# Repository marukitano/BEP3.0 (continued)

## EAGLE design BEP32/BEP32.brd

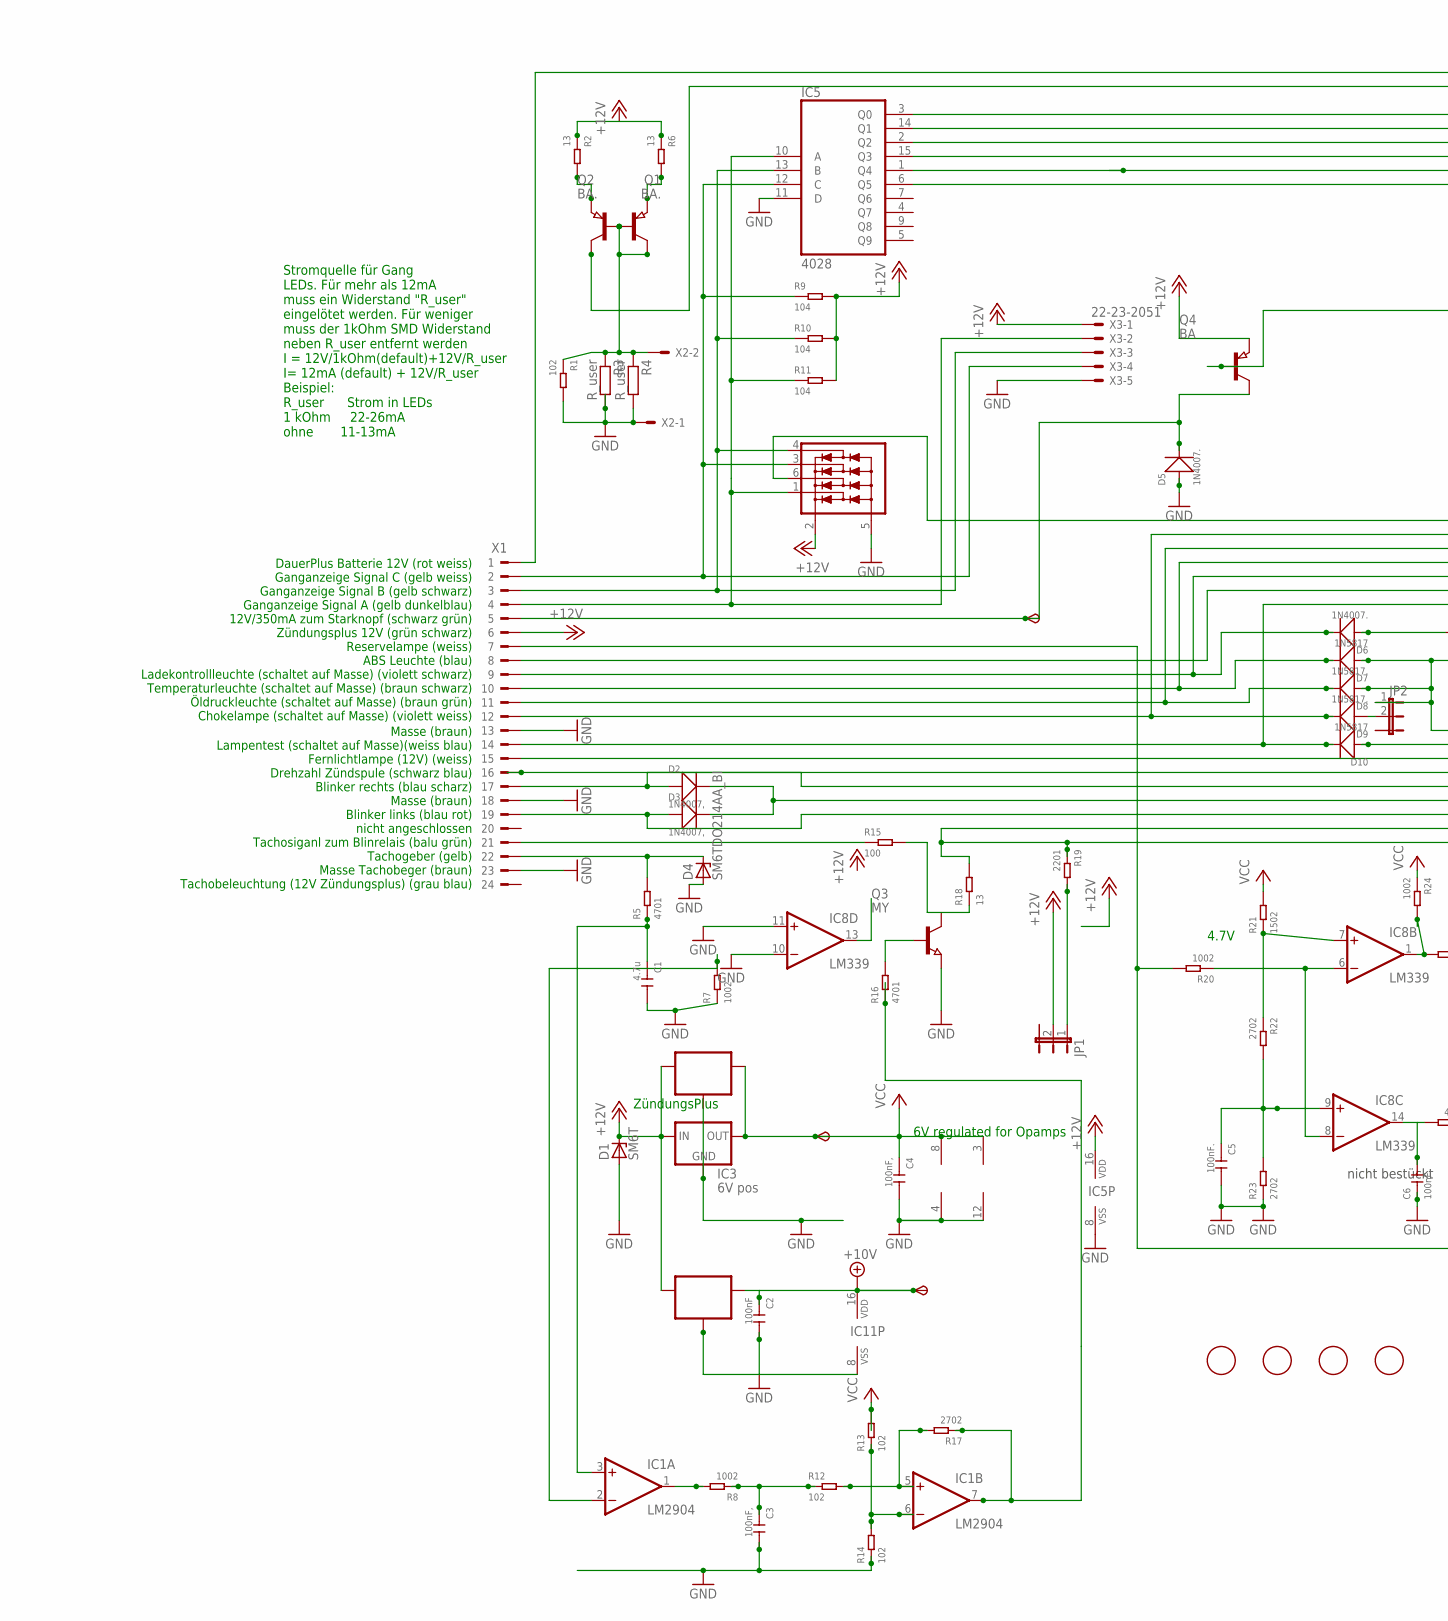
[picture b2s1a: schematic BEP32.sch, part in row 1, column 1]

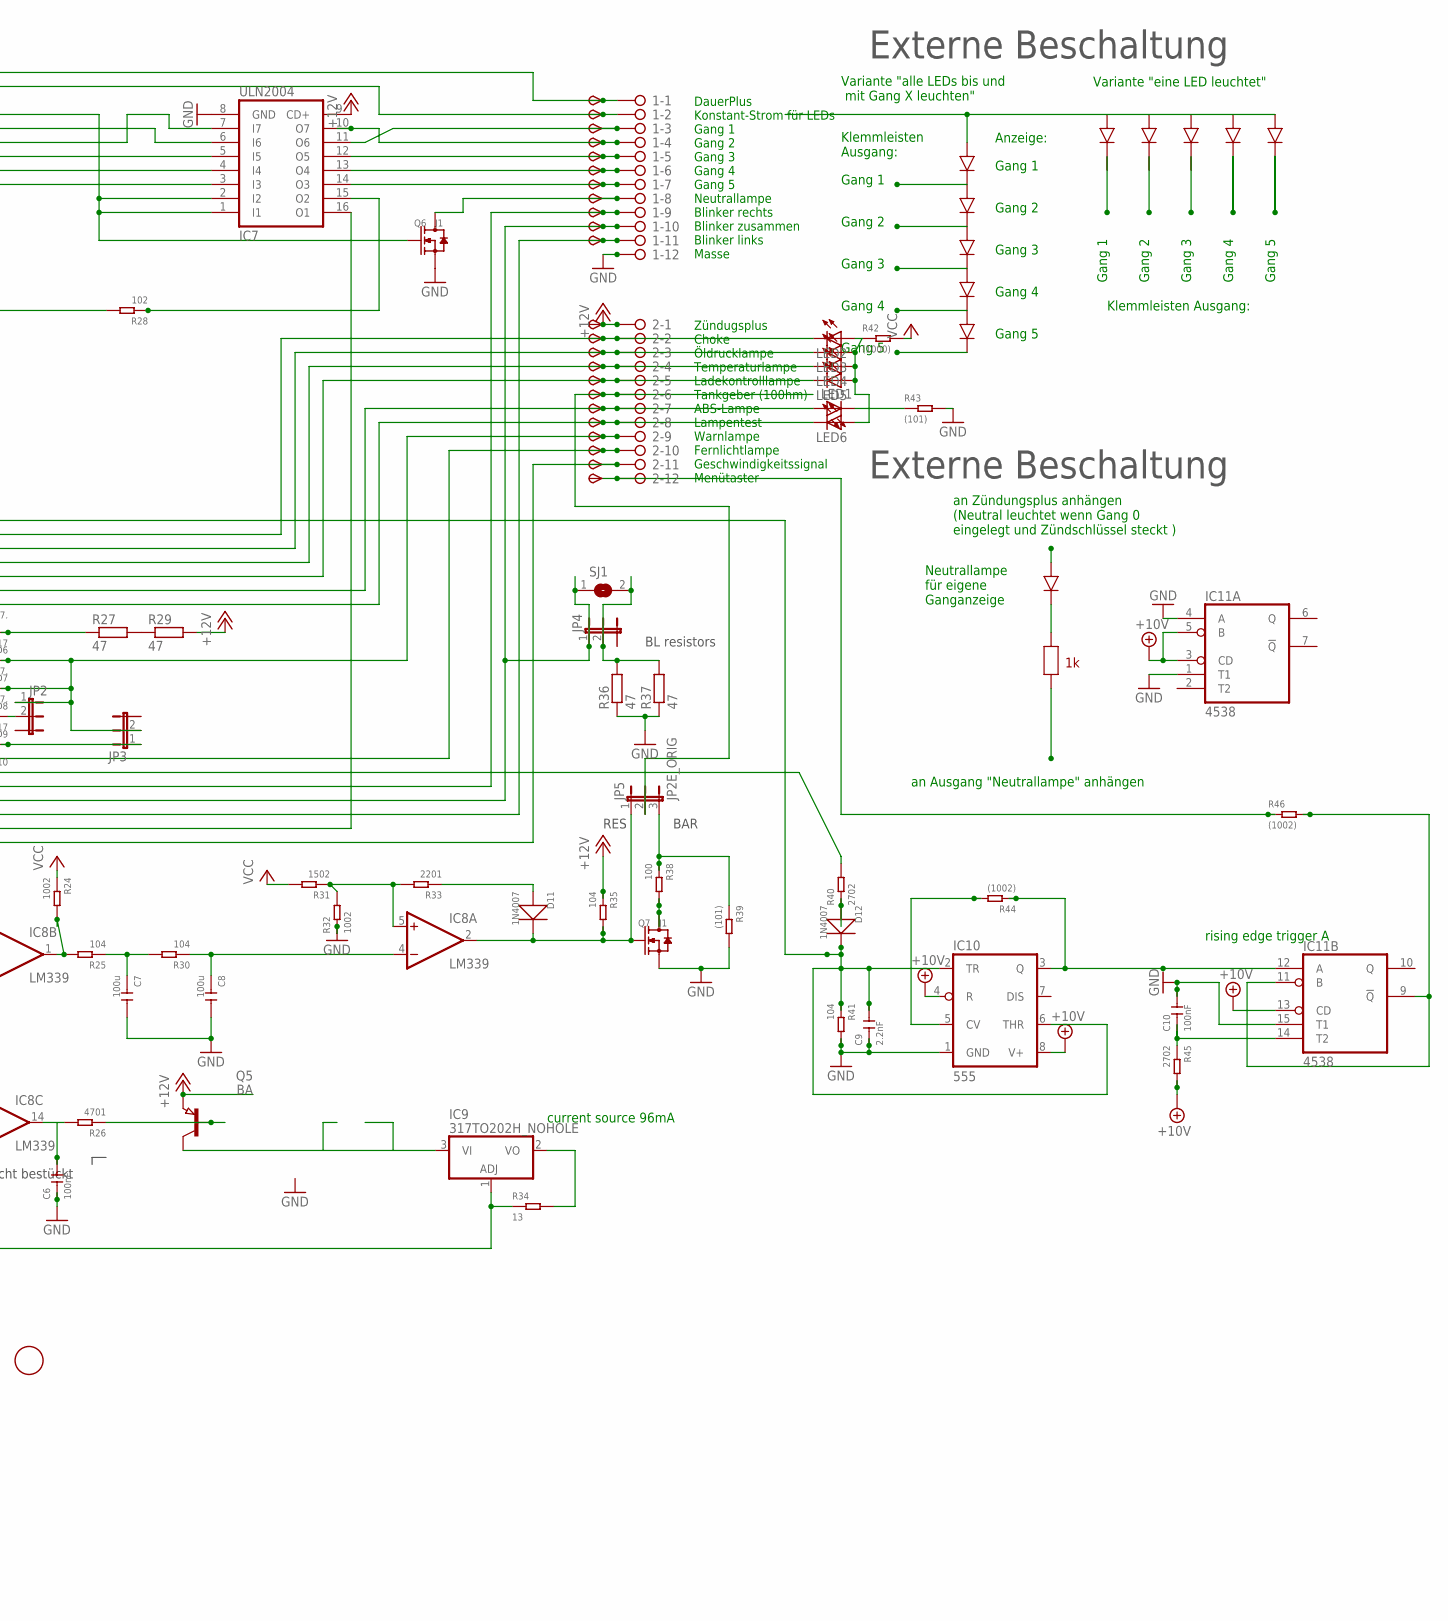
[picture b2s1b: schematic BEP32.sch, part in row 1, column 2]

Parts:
1, 2: 2081-1132; 12-PIN
6V, 10V: TPSB2.0; B2.0
C1: 4.7u; C0805
C2, C10: 100nF; C0805
C3, C4: 100nF,; C0805
C5, C6: 100nF.; C0805
C7, C8: 100u; C1206
C9: 2.2nF; C0805
D1: SM6T; DO214AA
D2, D3: 1N4007,; DO-214AC
D4: SM6TDO214AA_BI; DO214AA_BI
D5, D6: 1N4007.; DO-214AC
D7, D10: 1N5817; DO-214AC_SLIM
D8, D9: 1N5817.; DO-214AC_SLIM
D11, D12: 1N4007; DO-214AC
FID1, FID2, FID3, FID4: FIDUCIAL; FIDUCIAL_1MM
IC1: LM2904; SO08
IC2: 78L06; SOT89_ROUND
IC3: 6V pos; 78LXX
IC4: 78L10; SOT89_ROUND
IC5: 4028; SO16
IC6: NUP4304SOT457_R; SOT457R_PHILIPS
IC7: ULN2004; SO16
IC8: LM339; SO14
IC9: 317TO202H_NOHOLE; TO220H_NOHOLE
IC10: 555; SO08
IC11: 4538; SO16
JP1, JP2, JP3, JP4: JP2EJP2_SMALLPADS; JP2_SMALLPADS
JP5: JP2E_ORIG; JP2_ORIG_SMALLPADS
LED1, LED2, LED3, LED4, LED5, LED6: LEDLD260; LD260
Q1, Q2: BA.; SOT89
Q3: MY; SOT89
Q4, Q5: BA; SOT89
Q6, Q7: J1; SOT-23
R1, R12, R13, R14, R28: 102; R0805
R2, R6, R18, R34: 13; R1206
R3, R4: R_user; R0805
R5, R16, R26: 4701; R0805
R7, R8, R20, R24, R32: 1002; R0805
R9, R10, R11, R25, R30, R35, R41: 104; R0805
R15, R38: 100; R0805
R17, R22, R23, R40, R45: 2702; R0805
R19, R33: 2201; R0805
R21, R31: 1502; R0805
R27, R29, R36, R37: 47; V235/17_1MM
R39, R43: (101); R0805
R42: (1000); R0805
R44, R46: (1002); R0805
SJ1: SJ
START: TPSB2.0; B2.0
TP1, TP2, TP3, TP4, TP5, TP6, TP7, TP8, TP9, TP10, TP11, TP12, TP13, TP16, TP17, TP18, TP19, TP21, TP22, TP23, TP25, TP26: TPSB2.0; B2.0
TP24: TPSB1,27; B1,27
X1: CON_BMWV2; 24-PIN_V2
X2: 22-23-2021
X3: 22-23-2051

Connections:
+10V: 10V.TP, C2.1, IC4.1 (OUT), IC10.4 (R), IC10.8 (V+), IC11.3 (CD), IC11.5 (B), IC11.13 (CD), IC11.16 (VDD), R45.2
+12V: 2.1, D1.C, IC2.3 (IN), IC3.IN, IC4.3 (IN), IC5.16 (VDD), IC6.2 (V+), IC7.9 (CD+), JP1.2, Q4.3 (E), Q5.3 (E), R2.1, R6.1, R9.2, R10.2, R11.2, R29.2, R35.1, TP12.TP, X1.6, X3.1
+12V1: IC1.7 (OUT), R16.1, R17.1
GND: 1.12, C1.2, C2.2, C3.2, C4.2, C5.2, C6.1, C7.2, C8.2, C9.1, C10.2, D1.A, D4.A, D5.1 (+), IC1.4 (V-), IC2.2 (GND), IC2.2@1 (GND), IC3.GND, IC4.2 (GND), IC4.2@1 (GND), IC5.8 (VSS), IC5.11 (D), IC6.5 (V-), IC7.8 (GND), IC8.10 (-IN), IC8.11 (+IN), IC8.12 (GND), IC10.1 (GND), IC11.1 (T1), IC11.4 (A), IC11.8 (VSS), IC11.15 (T1), Q3.3 (E), Q6.2 (S), Q7.2 (S), R1.2, R3.2, R4.2, R7.1, R14.1, R23.1, R32.1, R36.1, R37.1, R39.2, R41.2, R43.2, X1.13, X1.18, X1.23, X2.1, X3.5
unnamed: 2.9, D7.1 (+), D8.1 (+), JP2.1, JP3.2, TP24.TP
unnamed: IC5.10 (A), IC6.1 (D1), R11.1, X1.4, X3.2
unnamed: IC5.13 (B), IC6.4 (D4), R10.1, X1.3, X3.3
unnamed: 2.7, LED1.A, TP22.TP, X1.8
unnamed: Q1.3 (E), R2.2
unnamed: D11.2 (-), IC8.2 (OUT), JP5.1, Q7.1 (G), R35.2
unnamed: IC1.2 (-IN), R7.2
unnamed: R27.2, R29.1
unnamed: Q2.3 (E), R6.2
unnamed: D5.2 (-), Q4.2 (C), START.TP, X1.5
unnamed: 2.2, D9.2 (-), LED2.K (C), TP16.TP, X1.12
unnamed: 2.3, D8.2 (-), LED3.K (C), TP17.TP, X1.11
unnamed: 2.4, D7.2 (-), LED4.K (C), TP18.TP, X1.10
unnamed: IC9.3 (VI), Q5.2 (C)
unnamed: IC8.6 (-IN), IC8.8 (-IN), R20.1
unnamed: IC5.12 (C), IC6.3 (D3), R9.1, X1.2, X3.4
unnamed: IC5.15 (Q3), IC7.5 (I5)
unnamed: 2.8, D10.2 (-), LED6.K (C), TP23.TP, X1.14
unnamed: 1.9, D2.1 (+), TP9.TP, X1.17
unnamed: 1.11, D3.1 (+), TP11.TP, X1.19
unnamed: IC11.9 (!Q), IC11.11 (B), R46.2
unnamed: D4.C, R5.2, X1.22
unnamed: C1.1, IC1.3 (+IN), R5.1
unnamed: 1.6, IC7.13 (O4), TP6.TP
unnamed: 1.7, IC7.14 (O3), TP7.TP
unnamed: 2.11, IC7.16 (O1), R18.2, R19.1, TP26.TP
unnamed: 2.6, JP5.2, TP21.TP
unnamed: JP1.1, R19.2
unnamed: C5.1, IC8.9 (+IN), R22.2, R23.2
unnamed: C6.2, IC8.14 (OUT), R26.2
unnamed: C9.2, D12.2 (-), IC6.6 (D2), IC10.2 (TR), IC10.6 (THR), R41.1
unnamed: LED1.K (C), R43.1
unnamed: IC9.1 (ADJ), R20.2, R34.1, X1.7
unnamed: Q5.1 (B), R26.1
unnamed: IC5.2 (Q2), IC7.7 (I7)
unnamed: 1.3, IC7.11 (O6), TP3.TP
unnamed: 1.5, IC7.12 (O5), TP5.TP
unnamed: LED2.A, LED3.A, LED4.A, LED5.A, LED6.A, R42.1
unnamed: R40.2, X1.16
unnamed: Q4.1 (B), R28.2
unnamed: IC5.3 (Q0), IC7.1 (I1), IC7.2 (I2), Q6.1 (G)
unnamed: C7.1, R25.1, R30.2
unnamed: C8.1, IC8.4 (-IN), R30.1
unnamed: IC8.5 (+IN), R31.1, R32.2, R33.2
unnamed: Q7.3 (D), R38.2
unnamed: D11.1 (+), R33.1
unnamed: IC5.1 (Q4), IC7.4 (I4)
unnamed: R15.1, X1.21
unnamed: 1.8, Q6.3 (D), TP8.TP
unnamed: 2.10, TP25.TP, X1.15
unnamed: D6.1 (+), R27.1
unnamed: 2.5, D6.2 (-), LED5.K (C), TP19.TP, X1.9
unnamed: IC5.14 (Q1), IC7.6 (I6)
unnamed: Q1.1 (B), Q2.1 (B), Q2.2 (C), R1.1, R3.1, R4.1, X2.2
unnamed: Q3.2 (C), R15.2, R18.1
unnamed: 1.2, Q1.2 (C), TP2.TP
unnamed: IC5.6 (Q5), IC7.3 (I3)
unnamed: IC9.2 (VO), R34.2
unnamed: IC10.5 (CV), R44.2
unnamed: 1.4, IC7.10 (O7), TP4.TP
unnamed: 1.1, TP1.TP, X1.1
unnamed: IC8.7 (+IN), R21.1, R22.1
unnamed: Q3.1 (B), R16.2
unnamed: IC10.3 (Q), IC11.12 (A), R44.1
unnamed: D12.1 (+), R40.1
unnamed: IC7.15 (O2), R28.1
unnamed: C10.1, IC11.14 (T2), R45.1
unnamed: 2.12, R46.1, TP13.TP
unnamed: IC1.1 (OUT), R8.2
unnamed: 1.10, D2.2 (-), D3.2 (-), JP4.1, SJ1.1, TP10.TP
unnamed: JP4.2, R36.2, R37.2, SJ1.2
unnamed: D9.1 (+), JP2.2
unnamed: C3.1, R8.1, R12.1
unnamed: IC1.5 (+IN), R12.2, R17.2
unnamed: D10.1 (+), JP3.1
unnamed: JP5.3, R38.1, R39.1
unnamed: IC1.6 (-IN), R13.1, R14.2
unnamed: IC8.1 (OUT), R24.2, R25.2
VCC: 6V.TP, C4.1, IC1.8 (V+), IC2.1 (OUT), IC3.OUT, IC8.3 (V+), R13.2, R21.2, R24.1, R31.2, R42.2

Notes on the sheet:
6V regulated for Opamps
current source 96mA
ZündungsPlus
Zündugsplus Choke Öldrucklampe Temperaturlampe Ladekontrolllampe Tankgeber (100hm) ABS-Lampe Lampentest Warnlampe Fernlichtlampe Geschwindigkeitssignal Menütaster
DauerPlus Konstant-Strom für LEDs Gang 1 Gang 2 Gang 3 Gang 4 Gang 5 Neutrallampe Blinker rechts Blinker zusammen Blinker links Masse
DauerPlus Batterie 12V (rot weiss) Ganganzeige Signal C (gelb weiss) Ganganzeige Signal B (gelb schwarz) Ganganzeige Signal A (gelb dunkelblau) 12V/350mA zum Starknopf (schwarz grün) Zündungsplus 12V (grün schwarz) Reservelampe (weiss) ABS Leuchte (blau) Ladekontrollleuchte (schaltet auf Masse) (vi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
Masse (braun) Lampentest (schaltet auf Masse)(weiss blau) Fernlichtlampe (12V) (weiss) Drehzahl Zündspule (schwarz blau) Blinker rechts (blau scharz) Masse (braun) Blinker links (blau rot) nicht angeschlossen Tachosiganl zum Blinrelais (balu grün) Tachogeber (gelb) Masse Tachobeger (braun) Tachobel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
4.7V
Stromquelle für Gang LEDs. Für mehr als 12mA muss ein Widerstand "R_user" eingelötet werden. Für weniger muss der 1kOhm SMD Widerstand neben R_user entfernt werden I = 12V/1kOhm(default)+12V/R_user I= 12mA (default) + 12V/R_user Beispiel: R_user Strom in LEDs 1 kOhm 22-26mA ohne 11-13mA
Gang 1
Gang 2
Gang 3
Gang 4
Gang 5
Variante "eine LED leuchtet"
Variante "alle LEDs bis und mit Gang X leuchten"
Klemmleisten Ausgang:
Klemmleisten Ausgang:
an Zündungsplus anhängen (Neutral leuchtet wenn Gang 0 eingelegt und Zündschlüssel steckt )
an Ausgang "Neutrallampe" anhängen
Neutrallampe für eigene Ganganzeige
Externe Beschaltung
Anzeige:
nicht bestückt
rising edge trigger A
BAR
RES
BL resistors

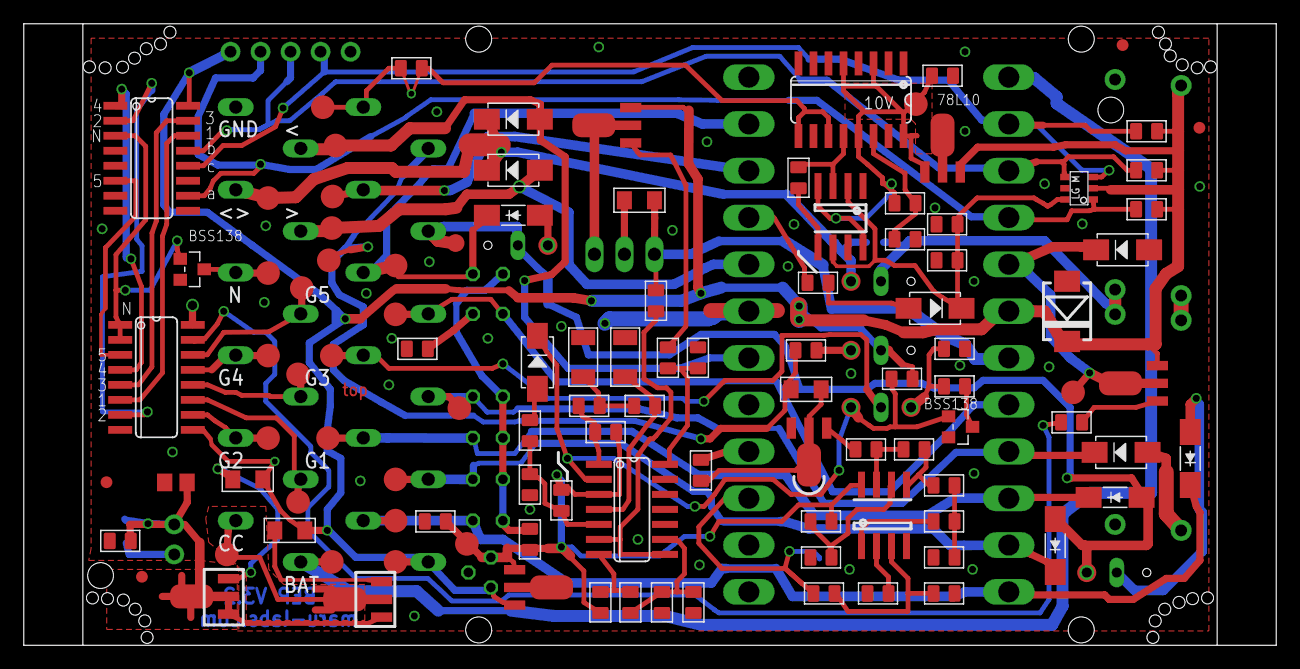
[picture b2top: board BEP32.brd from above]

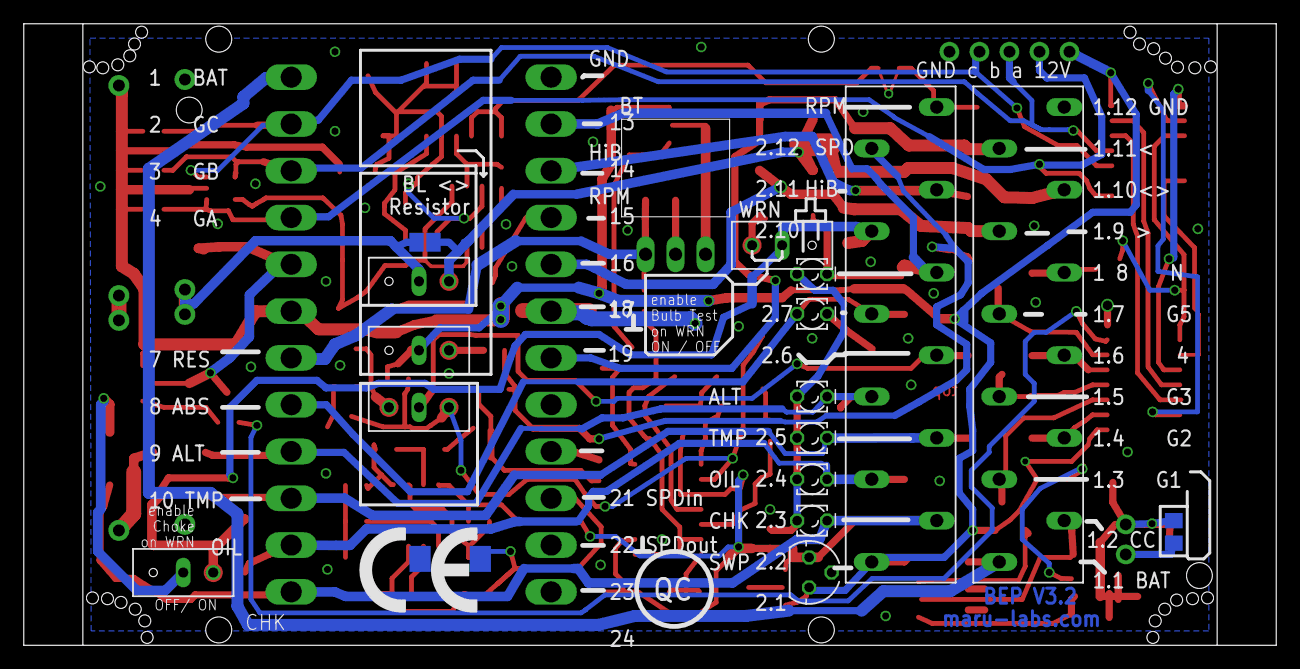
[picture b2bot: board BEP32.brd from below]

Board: 2 copper layers, 106.0 x 52.6 mm, 134 parts (26 on the bottom side), 83 nets.

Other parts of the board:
U$1: CE_10.00
